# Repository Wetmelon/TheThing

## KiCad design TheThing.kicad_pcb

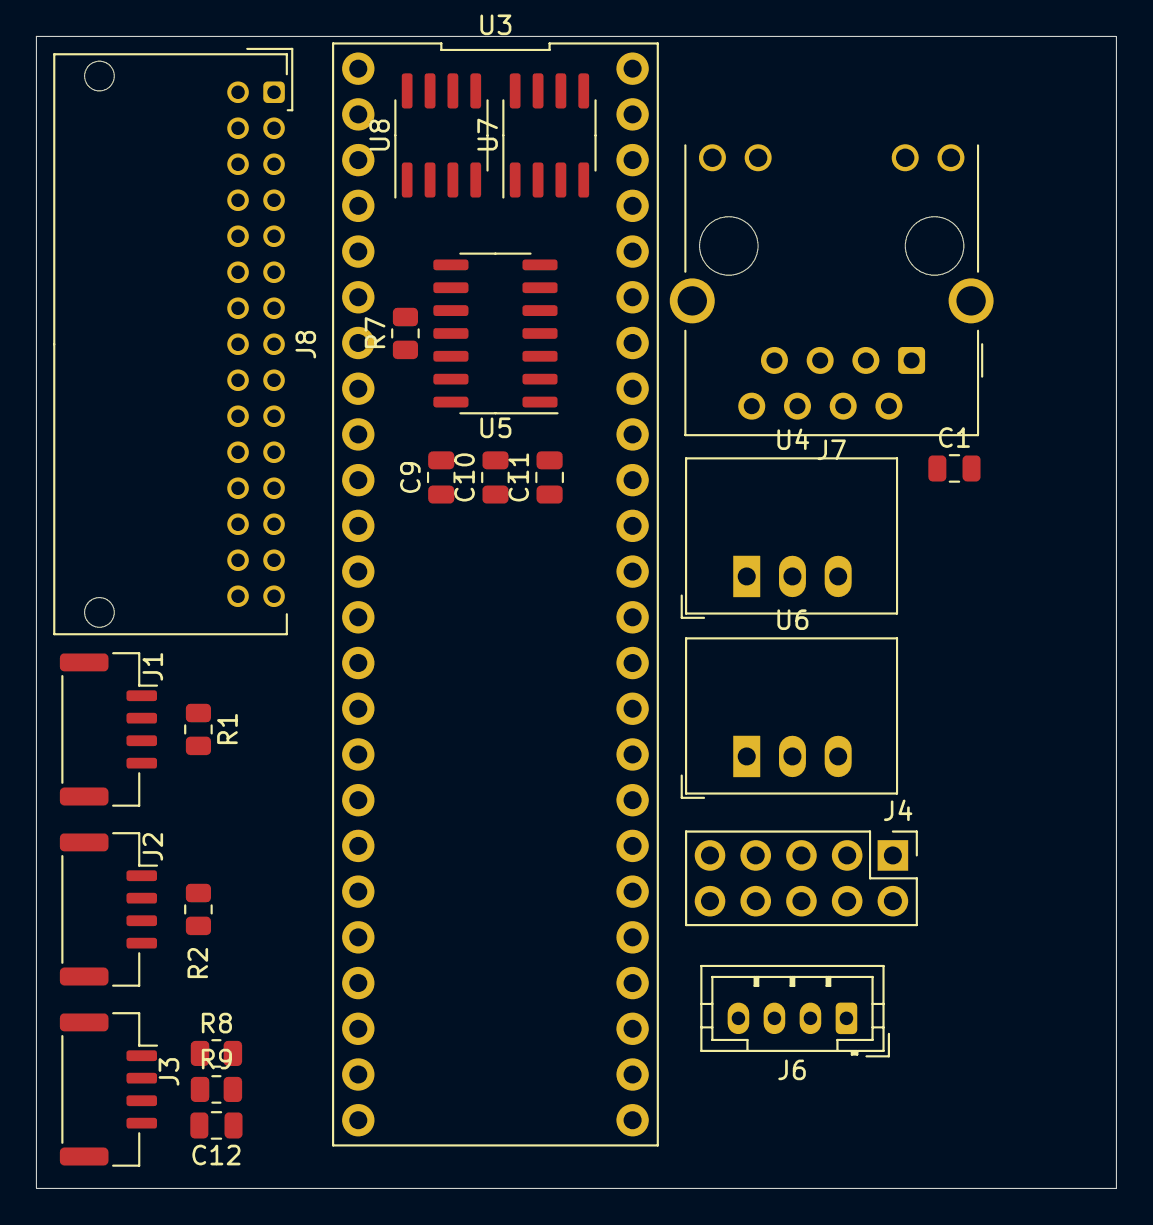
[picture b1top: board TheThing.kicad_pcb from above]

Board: 4 copper layers, 60.0 x 64.0 mm, 23 parts (0 on the bottom side), 44 nets, no tracks yet.

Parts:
C1: 0.1uF; C_0805_2012Metric
C9, C10, C11: 10nF; C_0805_2012Metric
C12: C_Small; C_0805_2012Metric
J1, J2, J3: Conn_01x04; JST_GH_SM04B-GHS-TB_1x04-1MP_P1.25mm_Horizontal
J4: Analog; PinHeader_2x05_P2.54mm_Vertical
J6: Qwiic; JST_PH_B4B-PH-K_1x04_P2.00mm_Vertical
J7: RJ45_Hanrun_HR911105A_Horizontal
J8: PUD; JST_PUD_S30B-PUDSS-1_2x15_P2.00mm_Horizontal
R1, R2: 120; R_0805_2012Metric
R7: R_Small; R_0805_2012Metric
R8, R9: 60; R_0805_2012Metric
U3: Teensy4.1
U4: R-78E12-0.5; Converter_DCDC_RECOM_R-78E-0.5_THT
U5: TJA1043T; SOIC-14_3.9x8.7mm_P1.27mm
U6: R-78E5.0-0.5; Converter_DCDC_RECOM_R-78E-0.5_THT
U7, U8: MCP2562-H-SN; SOIC-8_3.9x4.9mm_P1.27mm

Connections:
+3.3V: J8.13, U3.15 (3.3V), U3.46 (3.3V), U7.5 (Vio), U8.5 (Vio)
+3V3: C9.1, U5.5 (VIO), U5.6 (EN), U5.14 (~STB)
+5V: C10.1, J6.2, J8.14, U3.48 (Vin), U5.3 (VCC), U6.3 (OUT), U7.3 (VDD), U8.3 (VDD)
+12V: J1.1, J2.1, J3.1, R7.1, U4.3 (OUT)
+BATT: C11.1, U4.1 (IN), U6.1 (IN)
/2: J8.1, U3.4 (~2)
/3: J8.2, U3.5 (~3)
/4: J8.3, U3.6 (~4)
/5: J8.4, U3.7 (~5)
/6: J8.5, U3.8 (~6)
/7: J8.6, U3.9 (~7)
/8: J8.7, U3.10 (~8)
/9: J8.8, U3.11 (~9)
/10: J8.9, U3.12 (~10)
/11: J8.10, U3.13 (~11)
/12: J8.11, U3.14 (~12)
/13: J8.12, U3.35 (~13)
/A0: J8.30, U3.36 (A0)
/A1: J8.29, U3.37 (A1)
/A2: J8.28, U3.38 (A2)
/A3: J8.27, U3.39 (A3)
/A4: J8.26, U3.40 (A4)
/A5: J8.25, U3.41 (A5)
/A6: J8.24, U3.42 (A6)
/A7: J8.23, U3.43 (A7)
/CAN1/CANH: J1.2, R1.1, U7.7 (CANH)
/CAN1/CANL: J1.3, R1.2, U7.6 (CANL)
/CAN2/CANH: J2.2, R2.1, U8.7 (CANH)
/CAN2/CANL: J2.3, R2.2, U8.6 (CANL)
/CAN FD/CANH: J3.2, R8.1, U5.13 (CANH)
/CAN FD/CANL: J3.3, R9.1, U5.12 (CANL)
/CANRX1: U3.45 (CAN_RX1), U7.4 (RXD)
/CANRX2: U3.2 (CAN_RX2), U8.4 (RXD)
/CANRX3: U3.22 (CAN_RX3), U5.4 (RXD)
/CANTX1: U3.44 (CAN_TX1), U7.1 (TXD)
/CANTX2: U3.3 (CAN_TX2), U8.1 (TXD)
/CANTX3: U3.23 (CAN_TX3), U5.1 (TXD)
/GND: J6.1, J8.15, J8.16, U3.1 (GND), U3.34 (GND), U3.47 (GND)
/SCL2: J6.4, U3.16 (SCL2)
/SDA2: J6.3, U3.17 (SDA2)
GNDD: C1.2, C9.2, C10.2, C11.2, C12.2, J1.4, J2.4, J3.4, J7.8, J7.10, J7.SH, U4.2 (GND), U5.2 (GND), U5.9 (WAKE), U6.2 (GND), U7.2 (VSS), U7.8 (STBY), U8.2 (VSS), U8.8 (STBY)
unnamed: C1.1, J7.4 (TCT), J7.5 (RCT)
unnamed: C12.1, R8.2, R9.2, U5.11 (SPLIT)
unnamed: R7.2, U5.10 (VBAT)
